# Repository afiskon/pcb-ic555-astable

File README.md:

# pcb-ic555-astable
PCB project - 555 timer in astable mode

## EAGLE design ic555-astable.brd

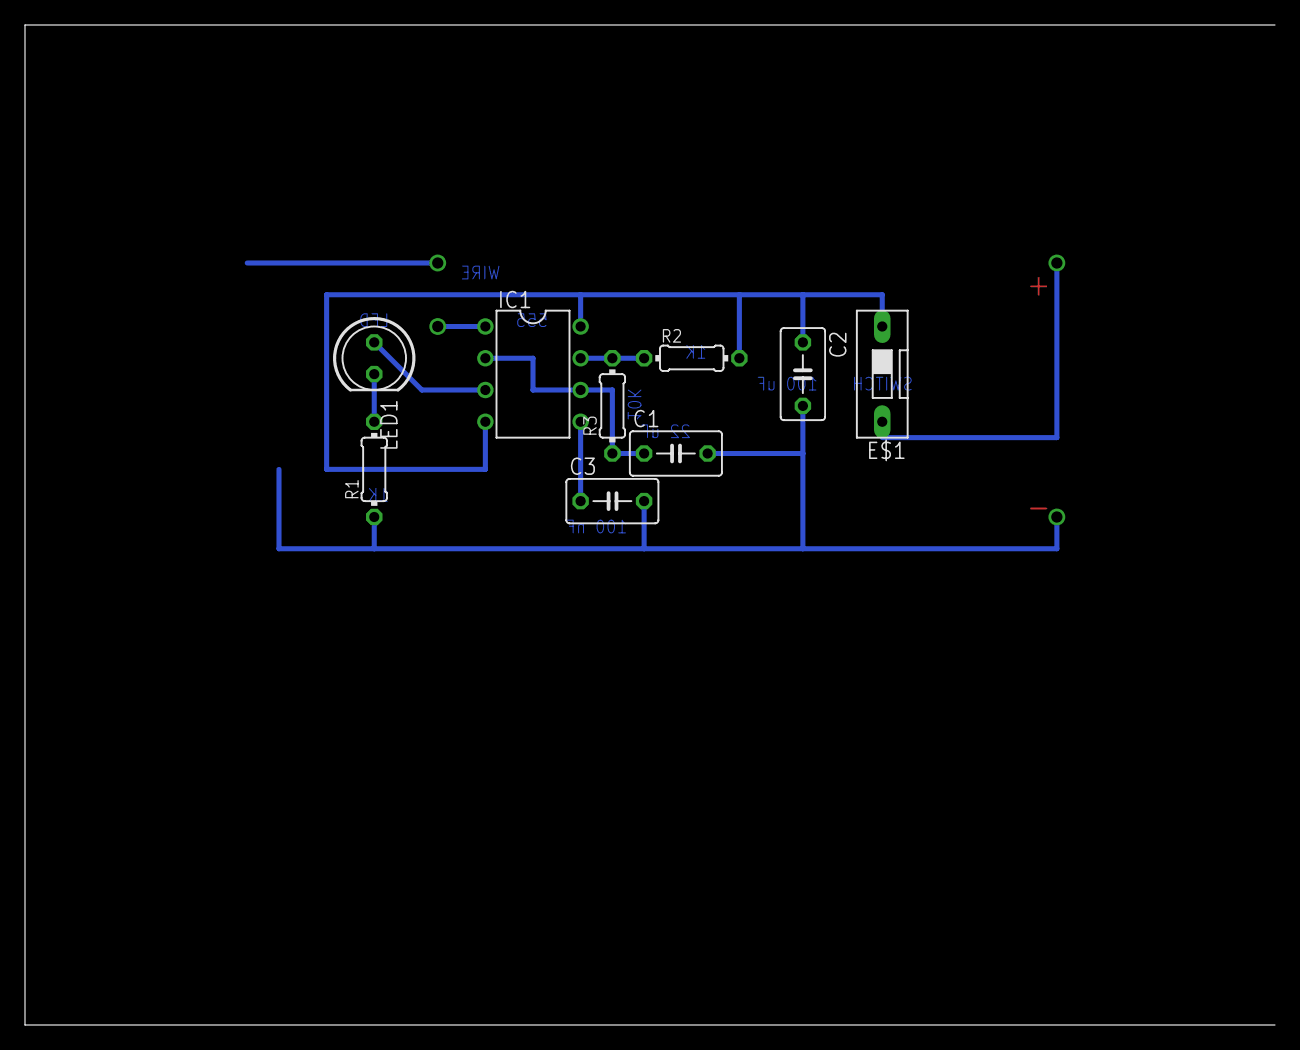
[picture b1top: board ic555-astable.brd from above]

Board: 2 copper layers, 100.0 x 80.0 mm, 9 parts (0 on the bottom side), 7 nets.

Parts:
C1: 22 uF; C050-035X075
C2: 100 uF; C050-035X075
C3: 100 nF; C050-035X075
E$1: DS-01
IC1: NE555N; DIL08
LED1: LED5MM
R1, R2: 1k; 0204/7
R3: 10k; 0204/7

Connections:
unnamed: C1.1, IC1.2, IC1.6, R3.1
unnamed: IC1.7, R2.1, R3.2
unnamed: C1.2, C2.2, C3.2, IC1.1, R1.1
unnamed: IC1.3, LED1.A
unnamed: LED1.K, R1.2
unnamed: C2.1, IC1.4, IC1.8, R2.2
unnamed: C3.1, IC1.5

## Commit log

2016-12-25 Project moved from a sandbox repository
2016-12-28 Fix board and schematic inconsistency
